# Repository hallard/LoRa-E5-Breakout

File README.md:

# LoRa-E5 breakout board

Mainly based on [LoRa-E5 mini](https://www.seeedstudio.com/LoRa-E5-mini-STM32WLE5JC-p-4869.html) board from Seedstudio, but since it was out of stock and I needed some specific wiring, I designed my own based on the Open Source design they made (thank for sharing)

I'm using mainly to flash custom firmware in it, and not using AT default firmware.

**These boards have been received, assembled, and works as expected**

- LoRa-E5 Module
- No USB/Serial, SMD FTDI 6 pins connector (**use 3.3V FTDI One, not 5V**)
- Exposed JTAG pins needed to flash module (PA13-SWDIO / PA14-SWCLK / RESET)
- Green Led on PB10
- Red Led on PB5
- Optional 2 Tactile Switch (boot and reset)
- 2 Antenna connector (u-Fl and SMA), select with 0 Ohm resistor
- I2C 4 pins location for "classic" sensors

## Detailed Description

No specific documentation for now, it's just a kind of wiring helper as schematic.

I also assume that you are familiar with all LoRaWAN stuff, all setup/infrastructure/network server/provisionning and other are out of scope of this repository.

## Schematics

## Boards 

~~You can order PCBs of this board at [PCBs.io][3]~~

- ~~[V1.0](https://PCBs.io/share/zM5GG)~~

 ~~PCBs.io give me some reward when you order my designed boards from their site. This is pretty good, because I can use these rewards to create and design new boards and order boards for a discounted price, so if you don't care about PCB manufacturer please use PCBs.io.~~

Looks like PCBs.io is gone, I do not have any rewards from PCBs.io since August 2020 and my free order placed after are still not received, so my guess they are not on business anymore.

So you can order the board on [oshpark](https://oshpark.com). 

- [V1.0](https://oshpark.com/shared_projects/pMgmywYX) 

It's a pitty after several discuss with OSHPark that I can't have any rewards for each people ordering my boards, this would allow me to order free PCB for shared projects and create new ones. For information my shared boards generated a total of **$285 162.00** orders at PCBs.io in 4 years, not bad at all :-)

Hoping one day OSHparks will thanks me giving them this market. 

### Assembled boards

**Top & bottom side V1.0**

### Bill Of Material

Nothing fancy, all components are 0805 and/or PTH and can be ordered almost anywhere (digikey, mouser, radiospare, ...). 
use only what you need dependings on what you want to do. 

Check Seeed format [BOM](https://github.com/hallard/LoRa-E5-Breakout/blob/main/LoRa-E5-Breakout-BOM.xlsx) File, check on [Seeed OPL](https://www.seeedstudio.com/opl.html) for manufacturer SKU match.

## Firmware

Before flashing any custom firmware, I strongly advise to test the board with default AT-Firmware to get the keys (even if you can use your own of course). 

Do do this, use 3.3V (and NOT 5V) FTDI USB/Serial adapter, I love this one from [sparkun](https://www.sparkfun.com/products/14050)

- Connect FTDI on the 6 pins dedicated header of the breakout
- use them a terminal application and open the port on your computer corresponding to the FTDI device
- set terminal settings to 9600 bauds 8 bits no parity 1 stop bit (8N1)
- check with at command `AT` device should anwser ``+AT: OK``

then get keys of the device

```
AT 
+AT: OK
AT+ID 
+ID: DevAddr, 24:90:05:44
+ID: DevEui, 2C:F7:F1:20:24:90:05:44
+ID: AppEui, 80:00:00:00:00:00:00:06
```

### Provision device on Network Server

For testing I'm always using The Things Network (TTN).
So next step is to provision this new device to TTN with the above keys (no need DevAddr) and get APPKEY from TTN (random generate) then get the key issued from TTN (we'll use it later below)

### Compile and flash Firmware

You can flash the board with excellent [mbed-os](https://os.mbed.com/mbed-os/) framework. 
Easy way is to use [mbed studio IDE](https://os.mbed.com/studio/). 
We added this board into [stm32customtargets](https://github.com/ARMmbed/stm32customtargets), don't hesitate to read the [readme](https://github.com/ARMmbed/stm32customtargets/blob/master/README.md). 
Finally the main firmware [mbed-os-example-lorawan](https://github.com/ARMmbed/mbed-os-example-lorawan) program.

Once IDE installed: 

- use `file` / `import program` and them import the example with URL `https://github.com/ARMmbed/mbed-os-example-lorawan`
- right click in the project name and select `Add Library` and enter `https://github.com/ARMmbed/stm32customtargets`
- open the file `custom_targets.json` from folder `stm32customtargets` and copy whole contents
- paste copied contents in the main root folder file `custom_targets.json` (yes replace the whole file) 
- open the file `mbed_app.json` and change parameters on the section `target_overrides`
    - LoRaWAN parameters such as frequency plan, OTAA, Duty Cycle, ...
    - replace keys with the ones you got from above step `lora.device-eui`, `lora.application-eui` and `lora.application-key`
- add the following section near the end of the file `mbed_app.json`.

```json
        "LORA_E5_BREAKOUT": {
            "stm32wl-lora-driver.rf_switch_config": "RBI_CONF_RFO_HP",
            "stm32wl-lora-driver.debug_tx": "PB_5",
            "stm32wl-lora-driver.debug_rx": "PB_10",
            "stm32wl-lora-driver.debug_invert": 1,
            "stm32wl-lora-driver.rf_switch_config": 2,
        }
```

When using any LoRa-E5 board you need to set the line `rf_switch_config` as above to `RBI_CONF_RFO_HP`, because hardware has not wired the mode `RBI_CONF_RFO_LP` and the stack for EU868 will try to use the `RBI_CONF_RFO_LP` (Low Power because 14dB max) path, and thus will result in unreliable signal (see #3). See this [post](https://forum.seeedstudio.com/t/lora-e5-fw-bug-tx-eu868-85ma-too-high-consumption/260126) and this [one](https://forum.rakwireless.com/t/rak3172-too-much-consumption-in-transmit-eu868/4781) for details.

Then on IDE select target "LORA_E5_BREAKOUT", build and flash with your favorite programmer (I'm using STLink) with GND/SWDIO/SWDCLK/RESET connected. 

Pay attention, that 1st time you need to erase SeeeStudio original firmware, make sure the Read Out Protection of the device is AA. If it is shown as BB, select AA and click Apply. See the end of this [section](https://wiki.seeedstudio.com/LoRa_E5_Dev_Board/#24-modify-your-device-eui-application-eui-application-key-and-your-lorawan-region) on how to do that with STM32CubeProgrammer.

### Build and Flash

From IDE you can build the example. If you plug your STLink while project opened, mbed ide will ask you if you want to set it up for this project/target, once approved you can compile, flash and even debug from mbed ide (need some tools installed, [read](https://os.mbed.com/docs/mbed-studio/current/monitor-debug/debugging-with-mbed-studio.html), very nice.

You can also see logs with the FTDI adapter and any Serial terminal set to 115200 bauds 8 bits no parity 1 stop bit (8N1)

```
Mbed LoRaWANStack initialized 
 CONFIRMED message retries : 3 
 Adaptive data  rate (ADR) - Enabled 
 Connection - In Progress ...
 Connection - Successful 
 Dummy Sensor Value = 3 
 23 bytes scheduled for transmission 
 Message Sent to Network Server 
 Dummy Sensor Value = 5 
 23 bytes scheduled for transmission 
 Message Sent to Network Server 
 Dummy Sensor Value = 7 
 23 bytes scheduled for transmission 
```

Green LED will be on when on receive mode and Red when sending data.

## License

This work is licensed under a [Creative Commons Attribution-NonCommercial-ShareAlike 4.0 International License](https://creativecommons.org/licenses/by-nc-sa/4.0/).
If you want to do commercial stuff with this project, please contact [CH2i company](https://ch2i.eu/en#support) so we can organize an simple agreement.

Original Seeed Studio reference design at https://wiki.seeedstudio.com/LoRa_E5_mini/

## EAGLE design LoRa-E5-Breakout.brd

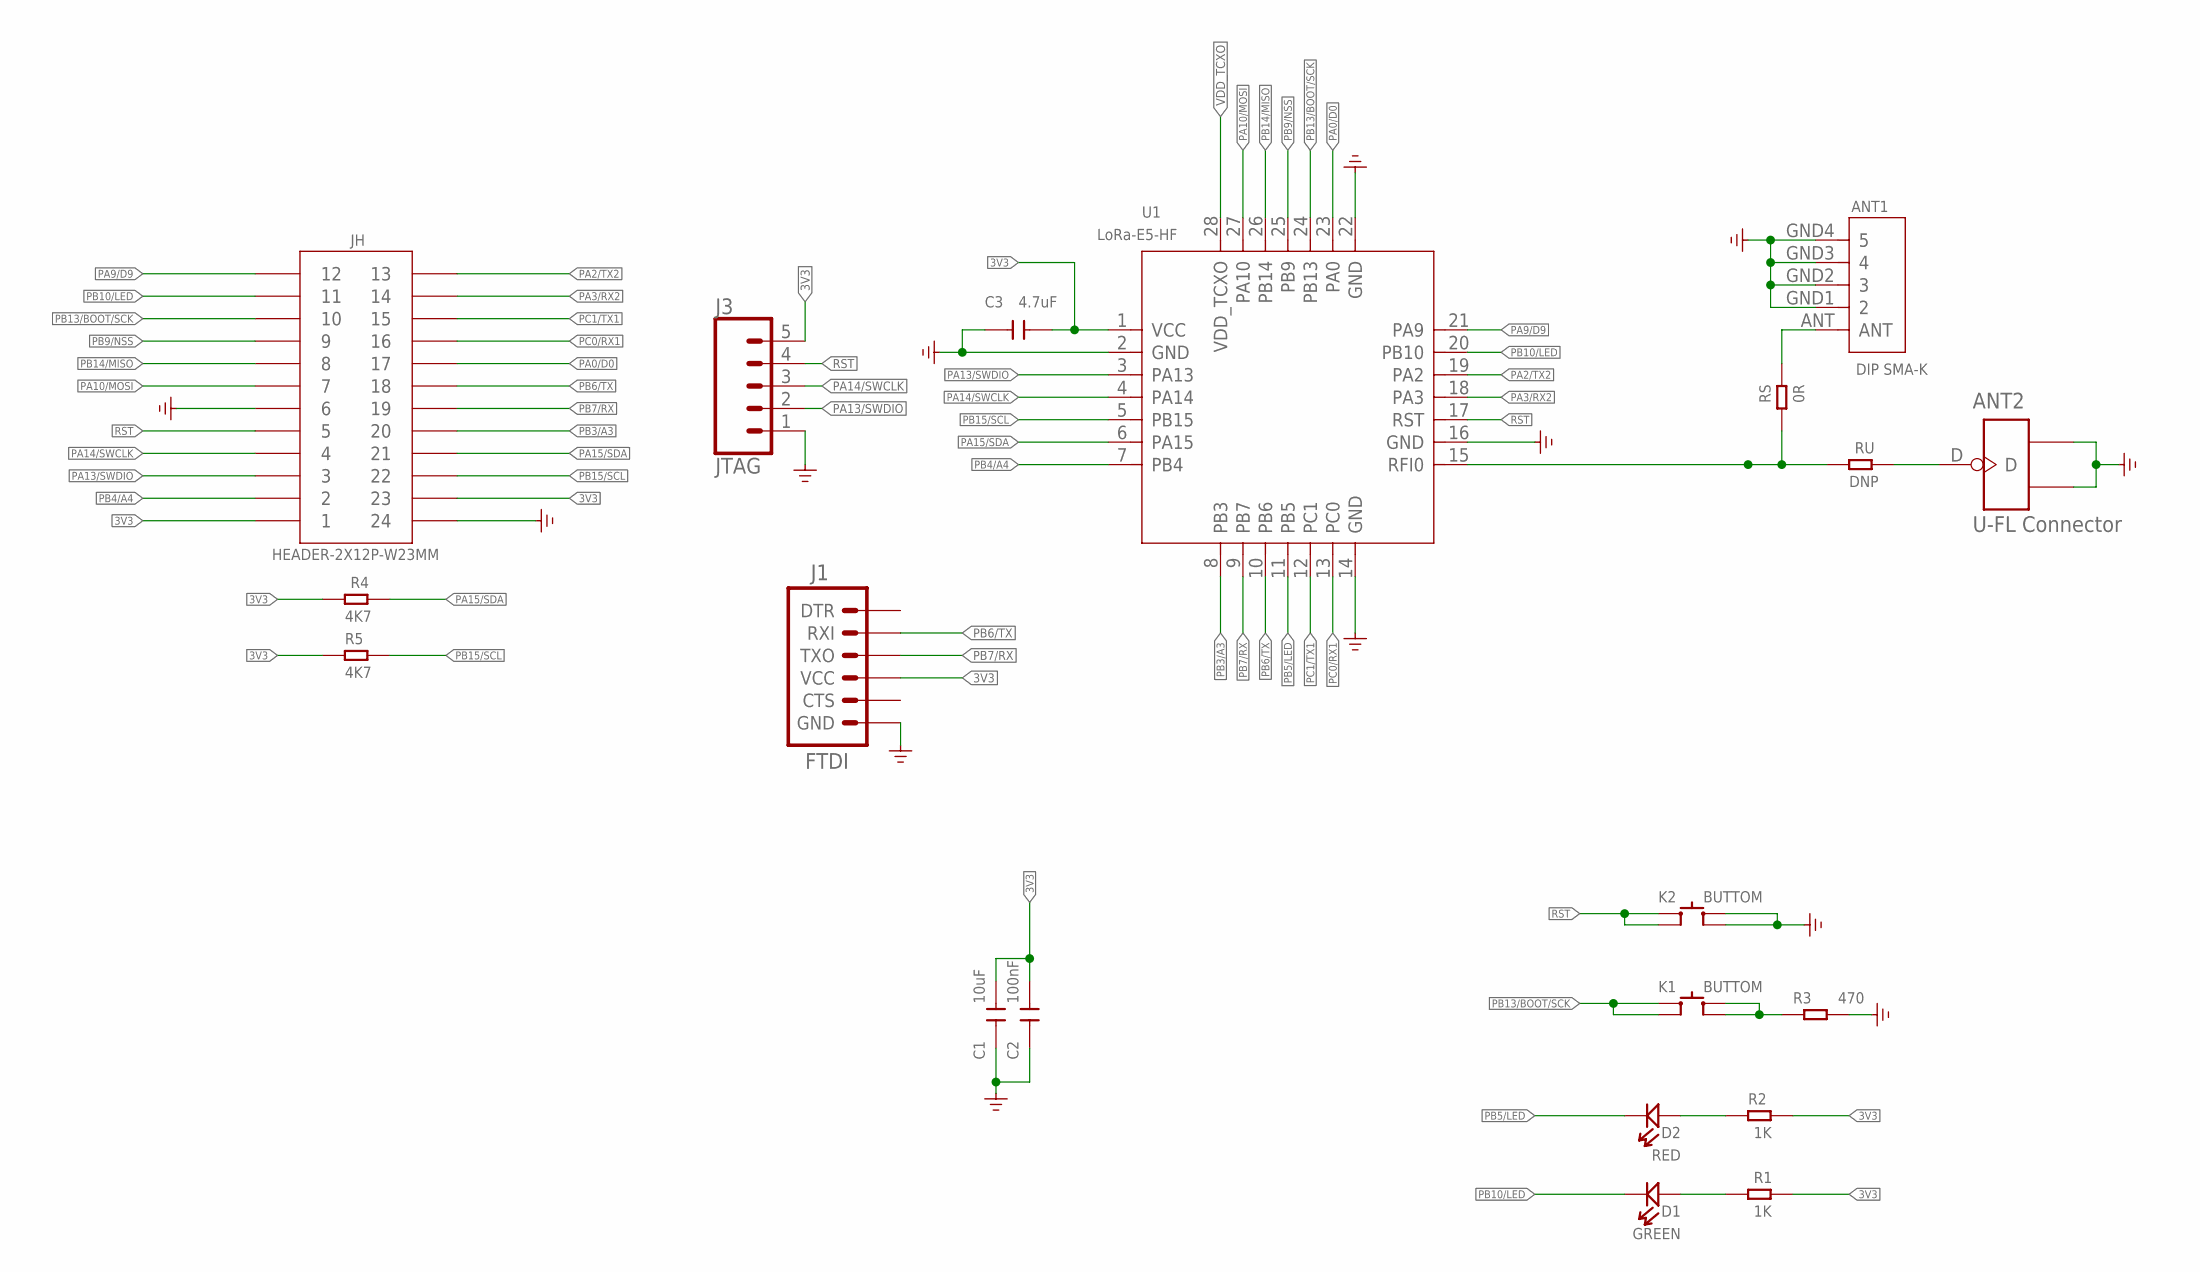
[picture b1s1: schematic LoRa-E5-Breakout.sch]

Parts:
ANT1: DIP SMA-K; SMA5P-SMD-5.1-6.5X6.5X16.5MM
ANT2: U-FL Connector; U-FL3P-SMD-2.6X2.6X1.0MM
C1: 10uF; C0805
C2: 100nF; C0805
C3: 4.7uF; C0805
D1: GREEN; LED-0805
D2: RED; LED-0805
J1: FTDI; 1X06-SMD_RA_MALE
J3: JTAG; 1X05_LOCK
JH: HEADER-2X12P-W23MM; H2X12-2.54-23MM
K1, K2: BUTTOM; SW4P-SMD-4.5X3.2X2.5MM
R1, R2: 1K; R0805
R3: 470; R0805
R4, R5: 4K7; R0805
RS: 0R; R0603
RU: DNP; R0603
U1: LoRa-E5-HF; MOUDLE28P-1.25-12X12X2.5MM

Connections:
3V3: C1.2, C2.2, C3.2, J1.4 (VCC), J3.5, JH.A1 (1), JH.B1 (1), JH.C11 (23), JH.D11 (23), JH.E1 (1), JH.E23 (23), JH.F1 (1), JH.F23 (23), R1.2, R2.2, R4.1, R5.1, U1.1 (VCC)
GND: ANT1.GND1 (2), ANT1.GND2 (3), ANT1.GND3 (4), ANT1.GND4 (5), ANT2.GND1, ANT2.GND2, C1.1, C2.1, C3.1, J1.6 (GND), J3.1, JH.A6 (6), JH.B6 (6), JH.C12 (24), JH.D12 (24), JH.E6 (6), JH.E24 (24), JH.F6 (6), JH.F24 (24), K2.3 (B0), K2.4 (B1), R3.2, U1.2 (GND), U1.14 (GND), U1.16 (GND), U1.22 (GND)
unnamed: D1.+, R1.1
unnamed: ANT2.D, RU.2
unnamed: D2.+, R2.1
unnamed: ANT1.ANT, RS.2
unnamed: K1.3 (B0), K1.4 (B1), R3.1
PA0/D0: JH.C5 (17), JH.D5 (17), JH.E17 (17), JH.F17 (17), U1.23 (PA0)
PA2/TX2: JH.C1 (13), JH.D1 (13), JH.E13 (13), JH.F13 (13), U1.19 (PA2)
PA3/RX2: JH.C2 (14), JH.D2 (14), JH.E14 (14), JH.F14 (14), U1.18 (PA3)
PA9/D9: JH.A12 (12), JH.B12 (12), JH.E12 (12), JH.F12 (12), U1.21 (PA9)
PA10/MOSI: JH.A7 (7), JH.B7 (7), JH.E7 (7), JH.F7 (7), U1.27 (PA10)
PA13/SWDIO: J3.2, JH.A3 (3), JH.B3 (3), JH.E3 (3), JH.F3 (3), U1.3 (PA13)
PA14/SWCLK: J3.3, JH.A4 (4), JH.B4 (4), JH.E4 (4), JH.F4 (4), U1.4 (PA14)
PA15/SDA: JH.C9 (21), JH.D9 (21), JH.E21 (21), JH.F21 (21), R4.2, U1.6 (PA15)
PB3/A3: JH.C8 (20), JH.D8 (20), JH.E20 (20), JH.F20 (20), U1.8 (PB3)
PB4/A4: JH.A2 (2), JH.B2 (2), JH.E2 (2), JH.F2 (2), U1.7 (PB4)
PB5/LED: D2.-, U1.11 (PB5)
PB6/TX: J1.2 (RXI), JH.C6 (18), JH.D6 (18), JH.E18 (18), JH.F18 (18), U1.10 (PB6)
PB7/RX: J1.3 (TXO), JH.C7 (19), JH.D7 (19), JH.E19 (19), JH.F19 (19), U1.9 (PB7)
PB9/NSS: JH.A9 (9), JH.B9 (9), JH.E9 (9), JH.F9 (9), U1.25 (PB9)
PB10/LED: D1.-, JH.A11 (11), JH.B11 (11), JH.E11 (11), JH.F11 (11), U1.20 (PB10)
PB13/BOOT/SCK: JH.A10 (10), JH.B10 (10), JH.E10 (10), JH.F10 (10), K1.1 (A0), K1.2 (A1), U1.24 (PB13)
PB14/MISO: JH.A8 (8), JH.B8 (8), JH.E8 (8), JH.F8 (8), U1.26 (PB14)
PB15/SCL: JH.C10 (22), JH.D10 (22), JH.E22 (22), JH.F22 (22), R5.2, U1.5 (PB15)
PC0/RX1: JH.C4 (16), JH.D4 (16), JH.E16 (16), JH.F16 (16), U1.13 (PC0)
PC1/TX1: JH.C3 (15), JH.D3 (15), JH.E15 (15), JH.F15 (15), U1.12 (PC1)
RF: RS.1, RU.1, U1.15 (RFI0)
RST: J3.4, JH.A5 (5), JH.B5 (5), JH.E5 (5), JH.F5 (5), K2.1 (A0), K2.2 (A1), U1.17 (RST)
VDD_TCXO: U1.28 (VDD_TCXO)

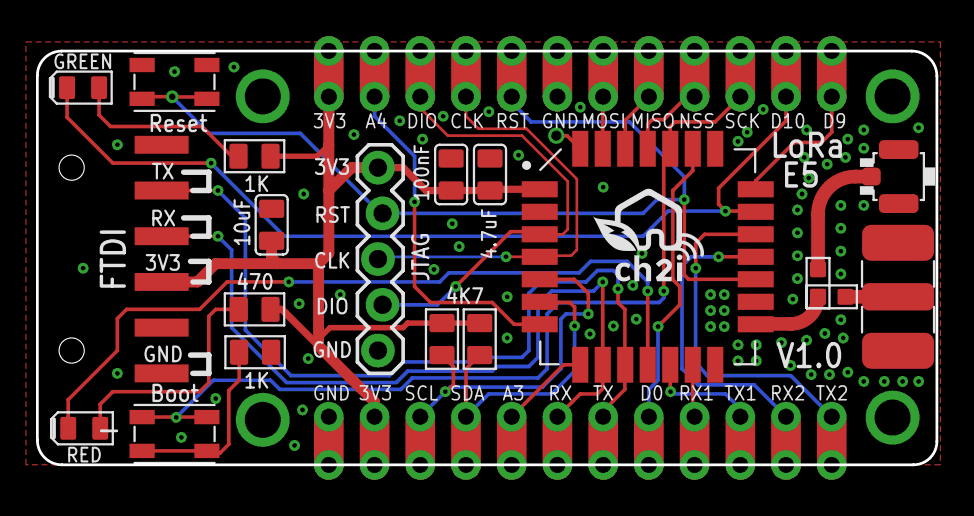
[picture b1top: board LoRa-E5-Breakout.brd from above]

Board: 2 copper layers, 50.0 x 23.0 mm, 22 parts (1 on the bottom side), 29 nets.

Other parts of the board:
U$1, U$2: LOGO_C2I_015

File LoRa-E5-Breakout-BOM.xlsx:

Designator | Seeed SKU | Qty | Description
U1 | 317990687 | 1 | LoRa-E5 STM32WLE5JC Module
C1 | 302010178 | 1 | SMD CAP Ceramic 10uF-25V-10%-X5R;0805
C2 | 302010165 | 1 | SMD CAP Ceramic 100nF-50V-10%-X7R;0805
C3 | 302010146 | 1 | SMD CAP Ceramic 4.7uF-25V-10%-X5R;0805
RS | 301012029 | 1 | SMD RES 0R-1%-1/10W;0603
R4,R5 | 301010306 | 2 | SMD RES 4.7K 0805
R1, R2 | 301010311 | 2 | SMD RES 1K 0805
R3 | 301010367 | 1 | SMD RES 470 0805
D1 | 304090043 | 1 | SMD LED Clear-Green
D2 | 304090042 | 1 | LED-SMD Red Diffused
K1,K2 | 311020518 | 2 | SMD Top Button 1.57N;4P-L4.6*W3.2*H2.5mm
ANT | 320111077 | 1 | SMD U-FL Female CONN-Gold;3P-L2.6*W2.6*H1.25mm

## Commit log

2021-06-03 Assembled boards
2021-06-03 added .DS_Store
2021-06-03 Added BOM File
2021-06-03 BOM link
2021-07-11 added firmware doc
2021-08-18 Fix bad power signal
2022-03-19 added documentation following #3
2022-03-19 fixed doc
2026-04-29 Add CC BY-NC-SA 4.0 LICENSE and update README license section

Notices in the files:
parts and their libraries:
SparkFun-Connectors: Licensing: Creative Commons ShareAlike 4.0 International - https://creativecommons.org/licenses/by-sa/4.0
